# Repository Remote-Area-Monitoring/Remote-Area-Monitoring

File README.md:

# Remote-Area-Monitoring

# Product Overview
Remote Area Monitoring is a system designed to reduce the risk of forest fires to populated areas. Our system provides forest management personnel with a data rich view of their environment. The data is collected by a mesh network of sensing nodes and recorded to provide a history of environmental conditions. RAM provides granular insight for the area’s most at risk. Our hope is that the information gathered by our system will aid those responsible for forest management in the prevention of forest fires by prompting preventative actions.

# Design Overview
### YouTube Video:

# Product Demonstration
### YouTube Video:

#### Additional Note

This project was completed as part of the University of Central Florida, Department of Electrical and Computer Engineering's senior design program. The project was active from the Spring 2022 semester to the Summer 2022 semester.

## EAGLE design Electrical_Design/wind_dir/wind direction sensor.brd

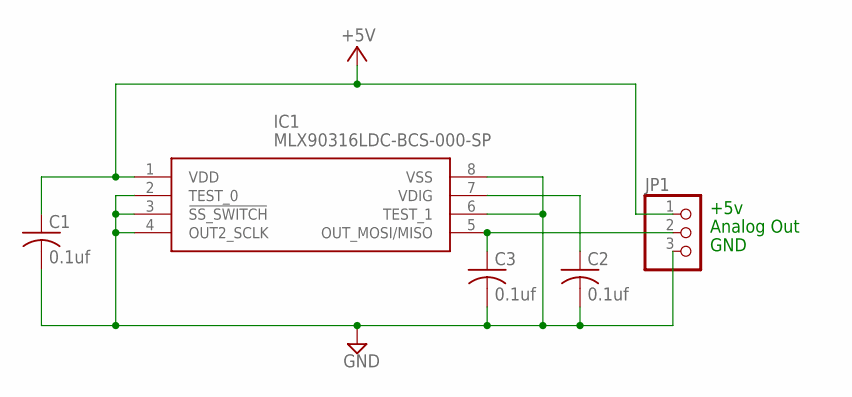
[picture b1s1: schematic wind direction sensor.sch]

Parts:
C1, C2, C3: 0.1uf; C1206K
IC1: MLX90316LDC-BCS-000-SP; SOIC127P600X172-8N
JP1: PINHD-1X3; 1X03

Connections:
+5V: C1.1, IC1.1 (VDD), JP1.1
GND: C1.2, C2.2, C3.2, IC1.2 (TEST_0), IC1.3 (!SS_SWITCH), IC1.4 (OUT2_SCLK), IC1.6 (TEST_1), IC1.8 (VSS), JP1.3
unnamed: C3.1, IC1.5 (OUT_MOSI/MISO), JP1.2
unnamed: C2.1, IC1.7 (VDIG)

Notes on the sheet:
Analog Out
+5v
GND

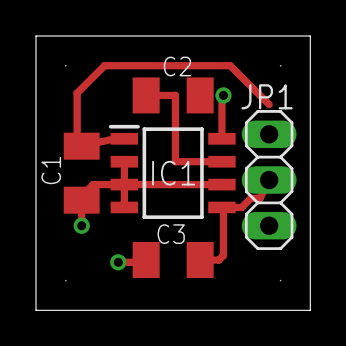
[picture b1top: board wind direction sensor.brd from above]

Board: 2 copper layers, 15.2 x 15.2 mm, 5 parts (0 on the bottom side), 4 nets.

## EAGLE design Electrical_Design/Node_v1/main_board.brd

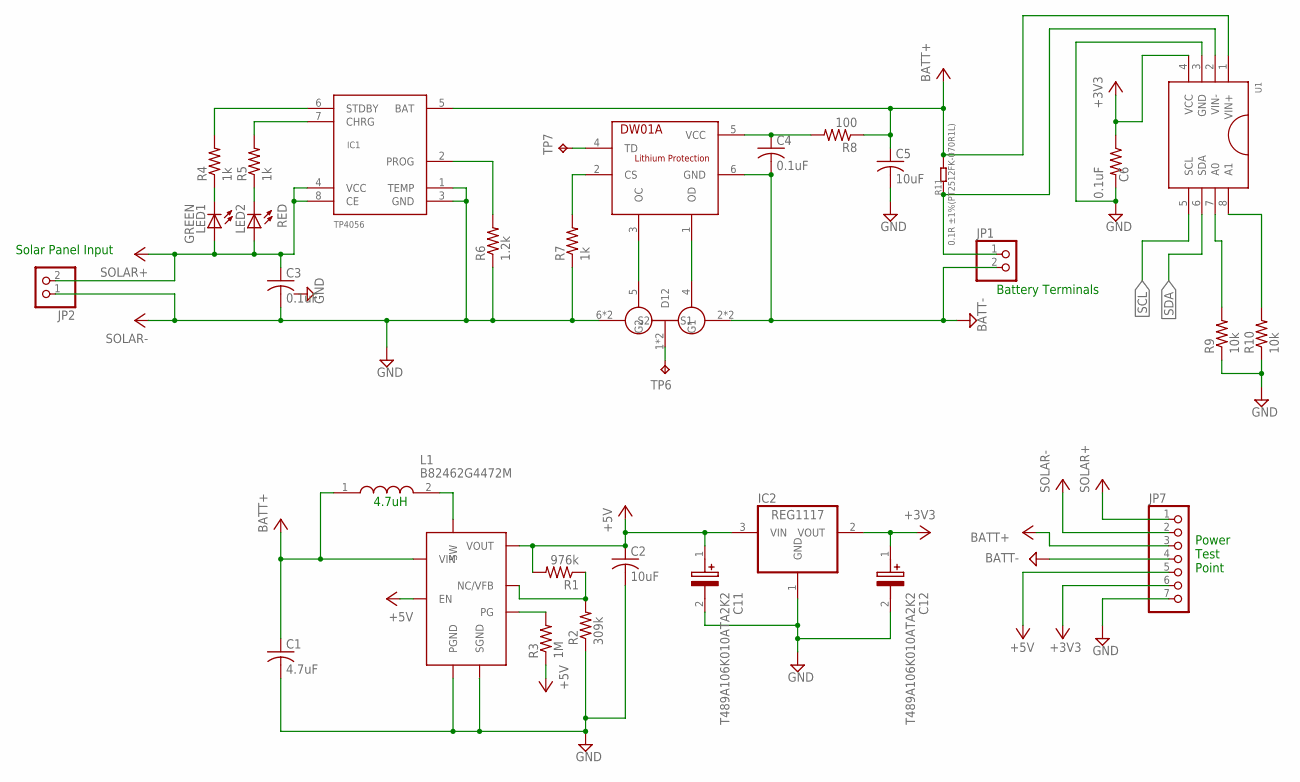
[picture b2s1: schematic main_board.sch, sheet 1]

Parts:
C1: 4.7uF; C1206; MPN GRM188R61E475KE11D
C2, C5: 10uF; C1206; MPN GRM188C80G106ME47D
C3, C4: 0.1uF; C1206; MPN C0805C104M5RACAUTO
C6: 0.1uF; R0402; MPN C0805C104M5RACAUTO
C11, C12: T489A106K010ATA2K2; T489A; MPN T489A106K010ATA2K2
IC1: TP4056; SOP-8
IC2: REG1117; SOT223
JP1, JP2: PINHD-1X2; 1X02
JP7: PINHD-1X7; 1X07
L1: B82462G4472M; MPN B82462G4472M000
LED1: GREEN; CHIPLED_1206; MPN HSMG-C170
LED2: RED; CHIPLED_1206; MPN SML-S13RTT86
R1: 976k; R1206; MPN CRCW0402976KFKED
R2: 309k; R1206; MPN ERJPA3F3093V
R3: 1M; R1206; MPN MCHVR02JTEY1004
R4, R5, R7: 1k; R1206; MPN MCT06030D1001BP500
R6: 1.2k; R1206; MPN RT0603DRE071K2L
R8: 100; R1206; MPN ZSR1000GTA
R9, R10: 10k; R1206; MPN RT0603BRB0710KL
R11: 0.1R ±1%(PT2512FK-070R1L); R2512; MPN PT2512FK-070R1L
TP6, TP7: TPPAD1-13; P1-13
U1: INA219; SOT23-8; MPN MAX6369KA+T
U$1: DW01A; SOT23-6
U$2: FS8205A; TSSOP8
U$3: MCP1642B; MPN MCP1642B-ADJI/MS

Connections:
+3V3: C6.1, C12.1 (+), IC2.2 (VOUT), JP7.6, U1.4 (VCC); also elsewhere on the board
+5V: C2.1, C11.1 (+), IC2.3 (VIN), JP7.5, R1.2, R3.1, U$3.EN, U$3.VOUT; also elsewhere on the board
BATT+: C1.1, C5.1, IC1.5 (BAT), JP7.3, L1.1, R8.1, R11.2, U1.1 (VIN+), U$3.VIN
BATT-: C4.2, JP1.2, JP7.4, U$1.6 (GND), U$2.2 (S1), U$2.3 (S1)
GND: C1.2, C2.2, C3.2, C5.2, C6.2, C11.2 (-), C12.2 (-), IC1.1 (TEMP), IC1.3 (GND), IC2.1 (GND), JP2.1, JP7.7, R2.1, R6.1, R7.1, R9.1, R10.1, U1.3 (GND), U$2.6 (S2), U$2.7 (S2), U$3.PGND, U$3.SGND; also elsewhere on the board
unnamed: R1.1, R2.2, U$3.NC (NC/VFB)
unnamed: R3.2, U$3.PG
unnamed: L1.2, U$3.SW
unnamed: IC1.6 (STDBY), R4.2
unnamed: IC1.7 (CHRG), R5.2
unnamed: LED2.C, R5.1
unnamed: LED1.C, R4.1
unnamed: U$1.3 (OC), U$2.5 (G2)
unnamed: U$1.1 (OD), U$2.4 (G1)
unnamed: IC1.2 (PROG), R6.2
unnamed: R7.2, U$1.2 (CS)
unnamed: C4.1, R8.2, U$1.5 (VCC)
unnamed: JP1.1, R11.1, U1.2 (VIN-)
unnamed: TP7.TP, U$1.4 (TD)
unnamed: TP6.TP, U$2.1 (D12), U$2.8 (D12)
unnamed: R9.2, U1.7 (A0)
unnamed: R10.2, U1.8 (A1)
SCL: U1.5 (SCL); also elsewhere on the board
SDA: U1.6 (SDA); also elsewhere on the board
SOLAR+: C3.1, IC1.4 (VCC), IC1.8 (CE), JP2.2, JP7.1, LED1.A, LED2.A
SOLAR-: JP7.2

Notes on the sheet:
4.7uH
Solar Panel Input
Battery Terminals
Power Test Point

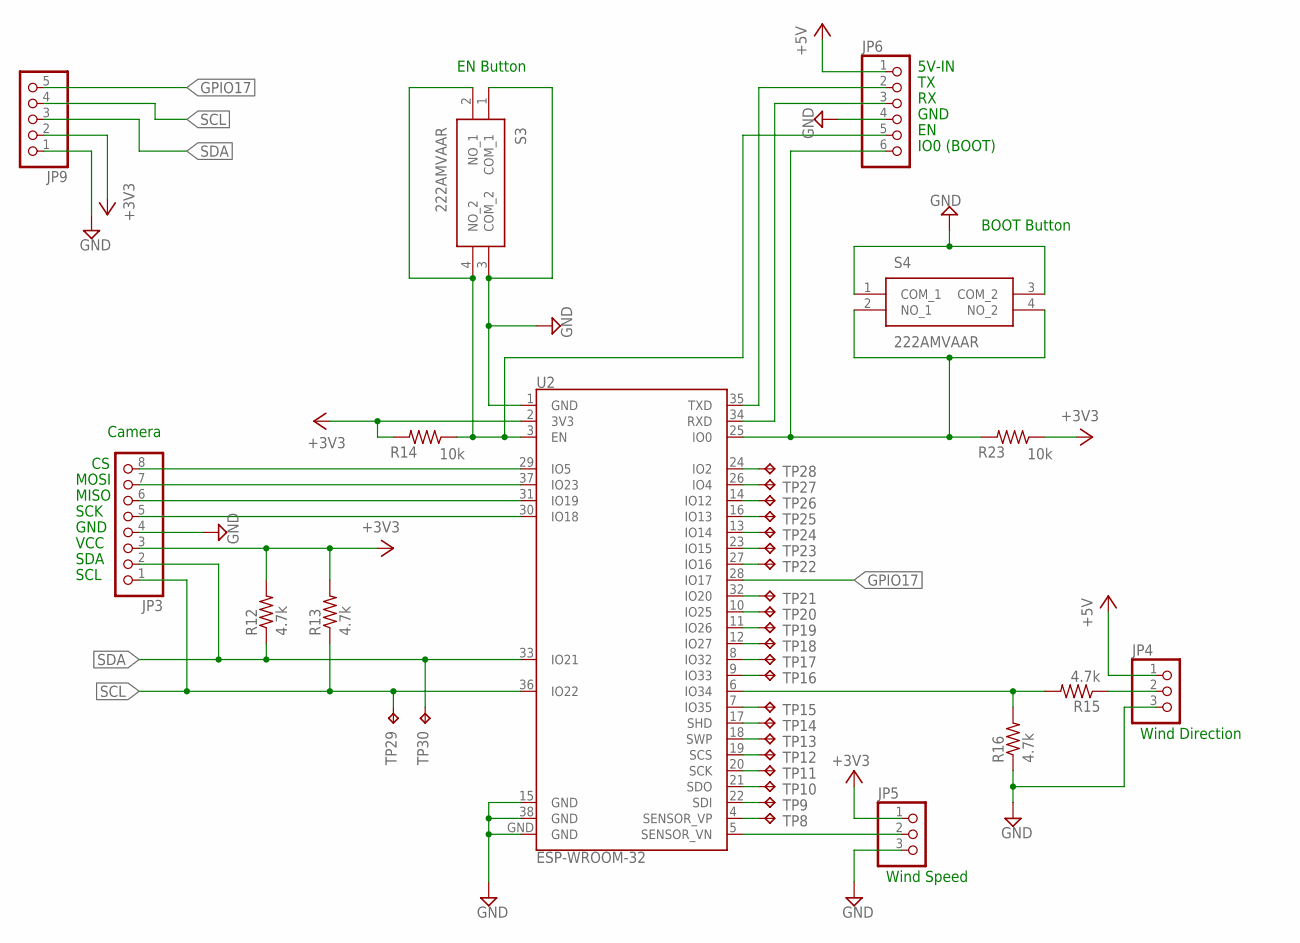
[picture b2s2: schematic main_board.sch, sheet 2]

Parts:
JP3: PINHD-1X8; 1X08; MPN PP5P-08BSS-155N
JP4, JP5: PINHD-1X3; 1X03; MPN 1X03
JP6: PINHD-1X6; 1X06; MPN 1X06
JP9: PINHD-1X5; 1X05
R12, R13, R15, R16: 4.7k; R1206; MPN MP000527
R14, R23: 10k; R1206; MPN RT0603BRB0710KL
S3, S4: 222AMVAAR
TP8, TP9, TP10, TP11, TP12, TP13, TP14, TP15, TP16, TP17, TP18, TP19, TP20, TP21, TP22, TP23, TP24, TP25, TP26, TP27, TP28, TP29, TP30: TPPAD1-13; P1-13
U2: ESP-WROOM-32

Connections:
+3V3: JP3.3, JP5.1, JP9.2, R12.2, R13.2, R14.2, R23.1, U2.2 (3V3); also elsewhere on the board
+5V: JP4.1, JP6.1; also elsewhere on the board
GND: JP3.4, JP4.3, JP5.3, JP6.4, JP9.1, R16.1, S3.1 (COM_1), S3.3 (COM_2), S4.1 (COM_1), S4.3 (COM_2), U2.1 (GND), U2.15 (GND), U2.38 (GND), U2.GND; also elsewhere on the board
GPIO17: JP9.5, U2.28 (IO17); also elsewhere on the board
unnamed: JP3.8, U2.29 (IO5)
unnamed: JP3.7, U2.37 (IO23)
unnamed: JP3.6, U2.31 (IO19)
unnamed: JP3.5, U2.30 (IO18)
unnamed: JP6.5, R14.1, S3.2 (NO_1), S3.4 (NO_2), U2.3 (EN)
unnamed: JP6.2, U2.35 (TXD)
unnamed: JP6.3, U2.34 (RXD)
unnamed: JP5.2, U2.5 (SENSOR_VN)
unnamed: JP6.6, R23.2, S4.2 (NO_1), S4.4 (NO_2), U2.25 (IO0)
unnamed: JP4.2, R15.1
unnamed: R15.2, R16.2, U2.6 (IO34)
unnamed: TP28.TP, U2.24 (IO2)
unnamed: TP27.TP, U2.26 (IO4)
unnamed: TP26.TP, U2.14 (IO12)
unnamed: TP25.TP, U2.16 (IO13)
unnamed: TP24.TP, U2.13 (IO14)
unnamed: TP23.TP, U2.23 (IO15)
unnamed: TP22.TP, U2.27 (IO16)
unnamed: TP21.TP, U2.32 (IO20)
unnamed: TP20.TP, U2.10 (IO25)
unnamed: TP19.TP, U2.11 (IO26)
unnamed: TP18.TP, U2.12 (IO27)
unnamed: TP17.TP, U2.8 (IO32)
unnamed: TP16.TP, U2.9 (IO33)
unnamed: TP15.TP, U2.7 (IO35)
unnamed: TP14.TP, U2.17 (SHD)
unnamed: TP13.TP, U2.18 (SWP)
unnamed: TP12.TP, U2.19 (SCS)
unnamed: TP11.TP, U2.20 (SCK)
unnamed: TP10.TP, U2.21 (SDO)
unnamed: TP9.TP, U2.22 (SDI)
unnamed: TP8.TP, U2.4 (SENSOR_VP)
SCL: JP3.1, JP9.4, R13.1, TP29.TP, U2.36 (IO22); also elsewhere on the board
SDA: JP3.2, JP9.3, R12.1, TP30.TP, U2.33 (IO21); also elsewhere on the board

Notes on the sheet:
Camera
MOSI
MISO
SCK
GND
VCC
SDA
SCL
5V-IN
IO0 (BOOT)
EN Button
BOOT Button
Wind Speed
Wind Direction

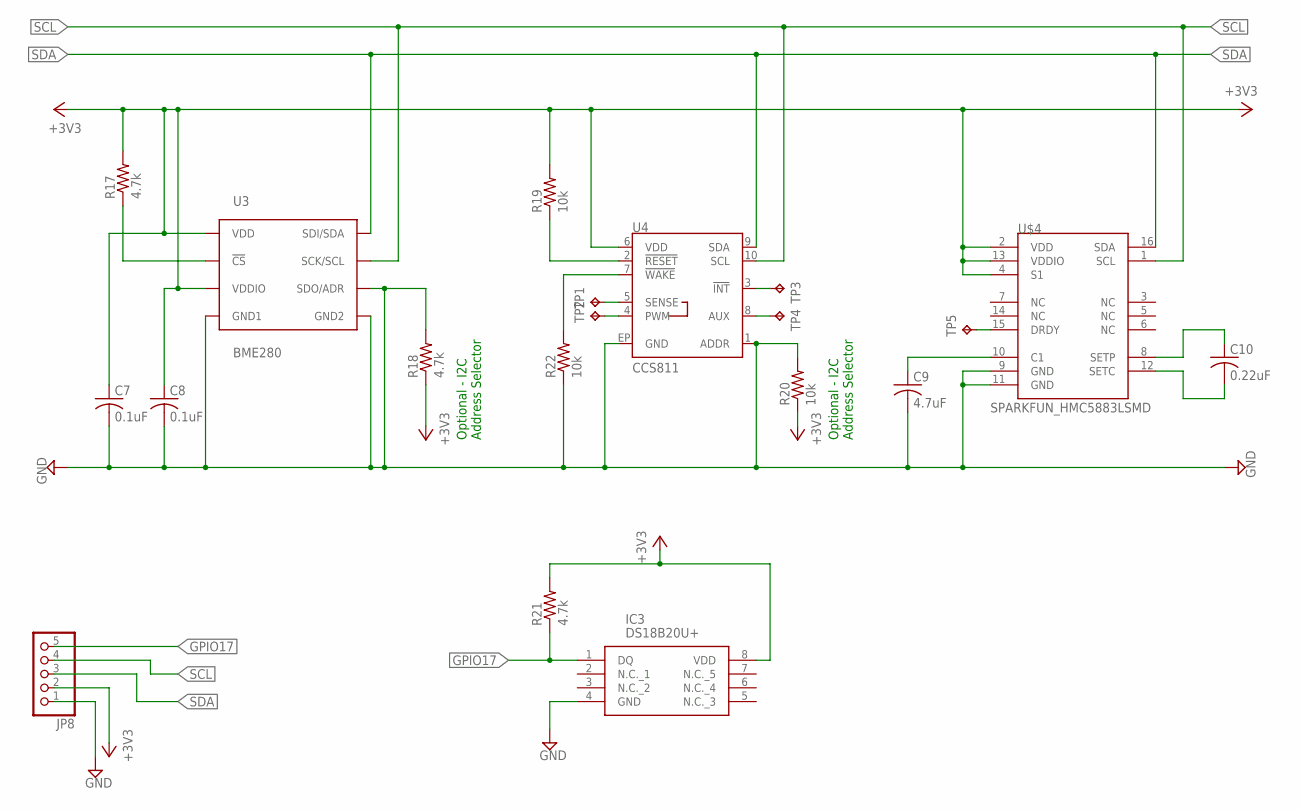
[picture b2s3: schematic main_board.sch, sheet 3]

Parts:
C7, C8: 0.1uF; C1206; MPN C0805C104M5RACAUTO
C9: 4.7uF; C1206; MPN GRM188R61E475KE11D
C10: 0.22uF; C1206; MPN C1005X7R1V224K050BE
IC3: DS18B20U+; SOP65P490X110-8N; MPN DS18B20U+T&R
JP8: PINHD-1X5; 1X05
R17, R18, R21: 4.7k; R1206; MPN MP000527
R19, R20, R22: 10k; R1206; MPN RT0603BRB0710KL
TP1, TP2, TP3, TP4, TP5: TPPAD1-13; P1-13
U3: BME280; BME280_LGA; MPN 2652
U4: CCS811; LGA10; MPN 3566
U$4: SPARKFUN_HMC5883LSMD; SPARKFUN_16LPCC

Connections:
+3V3: C7.1, C8.1, IC3.8 (VDD), JP8.2, R17.2, R18.1, R19.2, R20.1, R21.2, U3.P$6 (VDDIO), U3.P$8 (VDD), U4.6 (VDD), U$4.2 (VDD), U$4.4 (S1), U$4.13 (VDDIO); also elsewhere on the board
GND: C7.2, C8.2, C9.2, IC3.4 (GND), JP8.1, R18.2, R20.2, R22.1, U3.P$1 (GND1), U3.P$5 (SDO/ADR), U3.P$7 (GND2), U4.1 (ADDR), U4.EP (GND), U$4.9 (GND), U$4.11 (GND); also elsewhere on the board
GPIO17: IC3.1 (DQ), JP8.5, R21.1; also elsewhere on the board
unnamed: R17.1, U3.P$2 (!CS)
unnamed: R19.1, U4.2 (!RESET!)
unnamed: C10.1, U$4.8 (SETP)
unnamed: C10.2, U$4.12 (SETC)
unnamed: R22.2, U4.7 (!WAKE!)
unnamed: C9.1, U$4.10 (C1)
unnamed: TP1.TP, U4.5 (SENSE)
unnamed: TP2.TP, U4.4 (PWM)
unnamed: TP3.TP, U4.3 (!INT!)
unnamed: TP4.TP, U4.8 (AUX)
unnamed: TP5.TP, U$4.15 (DRDY)
SCL: JP8.4, U3.P$4 (SCK/SCL), U4.10 (SCL), U$4.1 (SCL); also elsewhere on the board
SDA: JP8.3, U3.P$3 (SDI/SDA), U4.9 (SDA), U$4.16 (SDA); also elsewhere on the board

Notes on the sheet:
Optional - I2C Address Selector

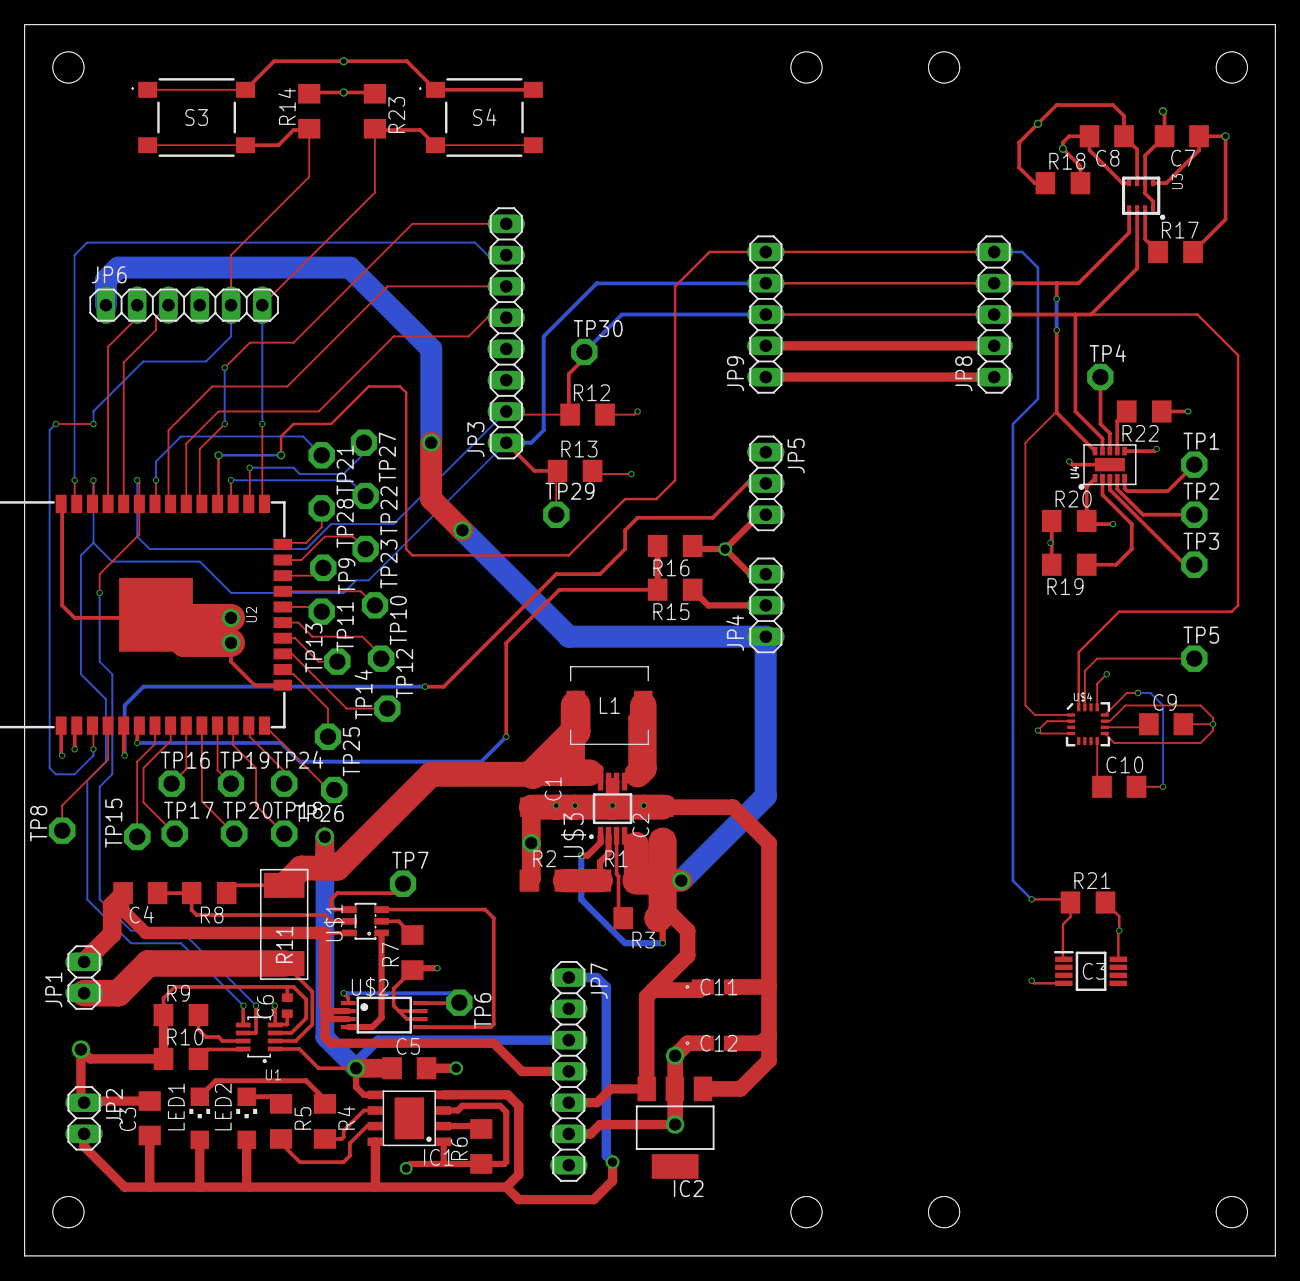
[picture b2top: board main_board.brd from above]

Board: 2 copper layers, 101.6 x 100.0 mm, 90 parts (0 on the bottom side), 69 nets.

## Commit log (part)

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2022-01-19 Initial FAQs
2022-01-19 Updates wording of FAQs
2022-03-11 Adds prototype ultrasonic anemometer v1 assembly -- Adds standalone ultrasonic sensor -- Adds UA STL files for printing
2022-03-12 Ignores MacOS system shortcut files
2022-03-12 Adds basic compass utility
2022-03-19 Adds basic networking prototype for the aggregator and a node using painless mesh
2022-03-28 Updates dev notes for prototyping
2022-04-01 Adds source for solar chargin testing
2022-04-02 Adds basic parser for sensor mesh proto
2022-04-02 Updates mesh node - adds soil sensor - fixes pin numbers -- Fixes crash in python parser when garbage data arrives
2022-04-04 Adds com port support for Mac -- Supports any node data as long as a node id is present
2022-04-04 node_all_sensors.ino deprecated - replaced with mesh_node_all_sensors.ino
2022-04-04 Updates dev notes - hall effect sensor for wind speed - testing notes
2022-04-04 Adds module for interacting with database files
2022-04-04 Adds early dev tool for visualizing sensor data -- example data graph
2022-04-04 Adds method for reading hall effect sensor RPM -- The pulses factor is a calculated value for 10,000rpm only - there are noise issues with the sensor itself - see dev_notes
2022-04-05 Proof of concept for Arducam mini camera module - camera communicates - bytes are recieved - need to interpret data and save to correctly formatted file
2022-04-06 Modified version of ArduCam example to save and dump serial commands to the log -- this can be used to reverse engineer the serial commands to get an image
2022-04-06 Script to read file in and print bytes -- used to get begining and end byte pattern of jpg
2022-04-06 Adds basic sketch to get soil moisture reading in ADC counts
2022-04-06 Adds example graph of solar data with most of the outliers removed -- resulting data causes y axis scales to change - results in harder to read data - need to set a fixed scale
2022-04-06 Adds com port reverse engineering steps to camera section
2022-04-07 Adds mac com port support
2022-04-21 Adds Eagle Project -- Completes power system schematics
2022-04-21 Adds current sensor to power page -- Adds microcontroller page
2022-04-22 Completes schematic layout
2022-04-23 Removes FAQs as they were no longer in line with project vision
2022-04-23 restore point to before backup file renaming
2022-04-24 Completes main board layout -- outstanding - isolate planes from divider line - remove planes from under esp antenna - generatre drc report
2022-05-22 Updates Schematics - adds BOM
2022-05-22 Adds initial aggregator node source -- ability to communicate with the network through the agreggator
2022-05-23 Adds map module - simple map to return html div for a map with a single point ploted by lat and lon
2022-05-23 Initial task list with resources and requirements
2022-05-24 Adds timekeeper to source
2022-05-24 Adds settings module - wrapper for ConfigParser with error handling
2022-05-24 Adds general settings file for sharing across modules
2022-05-24 Adds module for controlling the mesh network - getting sensor data from nodes and inserting to database
2022-05-24 Adds module for managing nodes - add nodes to configuration database
2022-05-25 Initial website structure -- map example page
2022-05-28 Adds line end character to end of topology string
2022-05-28 Adds break to top of page for formatting
2022-05-30 Adds 3d model for circuit board solder paste fixture
2022-05-31 Updates path to get full path from relative file name
2022-05-31 Adds method to remove records
2022-05-31 Adds demo prep section
2022-05-31 Adds table showing nodes information to website
2022-05-31 Adds default database path location
2022-05-31 Adds node table page -- adds mesh and nodes database global objects
2022-06-03 Adds graph generation utility
2022-06-03 Adds website info - receive timeout
2022-06-03 Updates databases with example data
2022-06-03 Adds page that when calls triggers a mesh network query -- Adds module to request the update page at a user defined interval
2022-06-03 Adds path for update page -- refactors module instantiations for mesh network
2022-06-03 Updates data
2022-06-04 Adds graphing utility to get example data from database
2022-06-04 Adds setting parameter for connection timeout - makes the website start faster for development when there is no network present
2022-06-04 Adds example map data - example nodes multipoint map -- new maps example page for testing maps and styles
2022-06-04 Adds maps example page for testing maps and styles
2022-06-14 Setting up github
2022-06-16 Removes deprecated setting
2022-06-16 Adds module for demonstrating graphs - empty
2022-06-16 Changes for troubleshooting file path settings
2022-06-16 First successful packetization
2022-06-16 Decodes packetized unsigned char arrays into pixel data byte array and writes to image file
2022-06-17 Adds method for receiving pixel data packes -- adds method for parsing image data -- adds proto method for wqriting image data to file
2022-06-17 Final camera only proto for sending packetized pixel data over mesh network - may need to mess with pixel data size on arduino for ram allocation
2022-06-17 Updates receive pixel data method - port.readall for pixel packets to avoid data loss -- Updates get image data for new format of packets - includes and adds metadata -- Updates method to update came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
2022-06-17 Adds module for handling image data -- method to validate pixel data has start and end bytes for jpeg -- method to get image div for html - need to modify for modularity, accept image data or node id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
2022-06-17 adds layout for example image page
2022-06-18 Adds database for images -- consider adding location to metadata
2022-06-21 Updates nodes database with new node config
2022-06-22 Adds method to update node status -- updates node generation main method
2022-06-22 Dev debug snapshot -- Updates method for updating image data
2022-06-22 Clears old data from images db -- updates image div to return list of divs
2022-06-22 Updates image example to print the most recent image for all nodes
2022-06-22 updates for mesh root node
2022-06-22 Adds image data task to updater
2022-06-22 Updates sensor data
2022-06-23 Adds copy/paste commands for using arduino serial monitor to debug python commands
2022-06-23 Adds image retry delay -- updates timings for mesh network
2022-06-23 Adds new image data for reduced image sizes
2022-06-23 Adds line to enable/disable debugging mode for mesh network to be used with serial monitor
2022-06-23 Adds dev tool for testing sending a full image as a single message - the result is that at 640x480 the compiler prevents the needed allocation of memory for the size of the message - the network may 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
2022-06-24 Contains double pixel data error
2022-06-24 activates proto node
2022-06-24 Adds pixel data size estimate
2022-06-24 Modifgies receive pixel data to prevent duplicate data on retry
2022-06-24 Adds sketch for proto node
2022-06-25 Adds module for getting sun info - sunrise, sunset, is_daylight
2022-06-25 Adds section for units
2022-06-25 Updates image database
2022-06-25 Adds module for converting units
2022-06-25 Adds module to manipulate node sensor data for node details page
2022-06-25 Initial page design for displaying data for a single node
2022-06-25 Adds a method for getting map of node location by node id
2022-06-25 Adds method to update connected nodes config file -- temporarily disables sunlight check for suntime bug with sunset
2022-06-25 Adds config file to tack connected nodes
2022-06-25 Adds method to get a time string with decimal accuracy - used to retain exact timestamp between conversions to string and back to timestamp -- Adds method to conver long time string back to timestamp
2022-06-25 Adds image view -- fixes connection status to match network -- adds node health readouts
2022-06-25 Adds page for displaying all nodes and their status
2022-06-26 Adds wind speed cal sketch using the pulseIn function
2022-06-26 Adds wind speed cal sketch using interupts
2022-06-27 Fixes bug - unpacking image data and metadata
2022-06-27 Fixes bug - too many concurrent calls for temperature on BME280
2022-06-27 Adds methods for humidity and pressure
2022-06-27 Adds methods - get date adjustable graph - get 24 hour temperature graph
2022-06-27 Adds node detail graph callback
2022-06-27 Updates databases
2022-06-29 Adds dashboard page - overview of network and environment
2022-06-29 Updates image sizing
2022-06-29 Updates size of single select graph
2022-06-29 Updates sizing - graph - image -- adds node id to top of page -- adds conversion for humidity gauge -- adjusts soil moisture gauge gradient
2022-06-29 Adds method to get min max and average by hour -- adds graph for min max and averate - only temperature implimented
2022-06-30 Adds signal strength function
2022-06-30 Adds custom css style for dbc radio-buttongroup
2022-06-30 Adds util for getting gauges - impliments dashboard gauges
2022-06-30 Adds support for custom css styles
2022-06-30 Adds remaining graph types to get all select graph method -- reorders traces to fix key order
2022-06-30 Adds proto network map - limited to a vertical only map
2022-06-30 Adds dashboard - gauges and content - gauges and min/max/avg graph
2022-06-30 Adds root node id, root location
2022-06-30 Adds empty module for mesh network status / management - demo todo list
2022-07-01 Adds a default - used to give user hints in settings
2022-07-01 Adds polling setting check to enable/disable sensor and image polling individually
2022-07-01 Adds connection strength to available graphs
2022-07-01 Adds connection strength to node detail graph
2022-07-01 Adds methods to get node network status graph -- adds proto heatmap
2022-07-01 Adds mesh overview, settings modal, quick toggles -- Adds mesh network node overview
2022-07-01 Adds logo files
2022-07-01 Removes night images -- removes excess data - keeps every 6th images
2022-07-01 Adds root signal strength
2022-07-01 changes homepage to land on dashboard
2022-07-01 moves legend to top of overview graph
2022-07-01 updates spacing at top of page
2022-07-02 Adds size printout to example images div
2022-07-02 Adds empty method for getting animated heatmap
2022-07-02 Updates bme280 mode - removes calibration - changes mode to forced as indoor navigation
2022-07-02 updates network indicator color for degraded status -- adds todo notes for bug fixes
2022-07-02 Adds module for estimating database size
2022-07-02 Adds image and sensor last updated configs
2022-07-02 Fixes max value lower than max measured for: pressure, co2 and tvoc
2022-07-02 Updates sensor database
2022-07-02 Adds cal log for 2 mag wind speed sensor
2022-07-07 Adds manual removal of errors in wind data
2022-07-07 Updates image data
2022-07-10 Adds reset function -- sets ccs811 to 60 second measure interval -- sets ccs811 environment offsets -- changes wind speed to raw data string -- adds raw data string for wind direction string
2022-07-10 Adds wind speed calibration factor
2022-07-10 Updates sensors data
2022-07-10 Updates wind speed removal
2022-07-11 Adds sketch for calibrating wind direction sensor
2022-07-11 Updates camera init - no longer blocks startup if camera is not found
2022-07-11 Adds environment data map
2022-07-11 Updates wind speed error removal
2022-07-11 Adds raw wind speed method
2022-07-11 Updates sensor data method to convert wind speed and direction data on intake
2022-07-11 Removes dev print statements
2022-07-20 Adds notification global toggle
2022-07-20 Adds check if node is connected for sensor data update -- fixes wind direction raw key -- adds second check for junk data when getting sensor data
2022-07-20 Fixes single select graph exceptions not catching KeyError
2022-07-20 Adds basic notifications page
2022-07-23 Adds secret files to git ignore - emails and creds
2022-07-23 Fixes error when parsing null raw data
2022-07-23 Adds methods: imperial, metric date strings, and human readable full timestring
2022-07-23 Adds notification monitor - daily summaries - node disconnected
2022-07-23 Adds page to manage and view notifications
2022-07-23 Adds notify section
2022-07-23 Adds example of secret.config
2022-07-23 Updates node config
2022-07-23 Adds alerts history database
2022-09-11 Final source code commit
